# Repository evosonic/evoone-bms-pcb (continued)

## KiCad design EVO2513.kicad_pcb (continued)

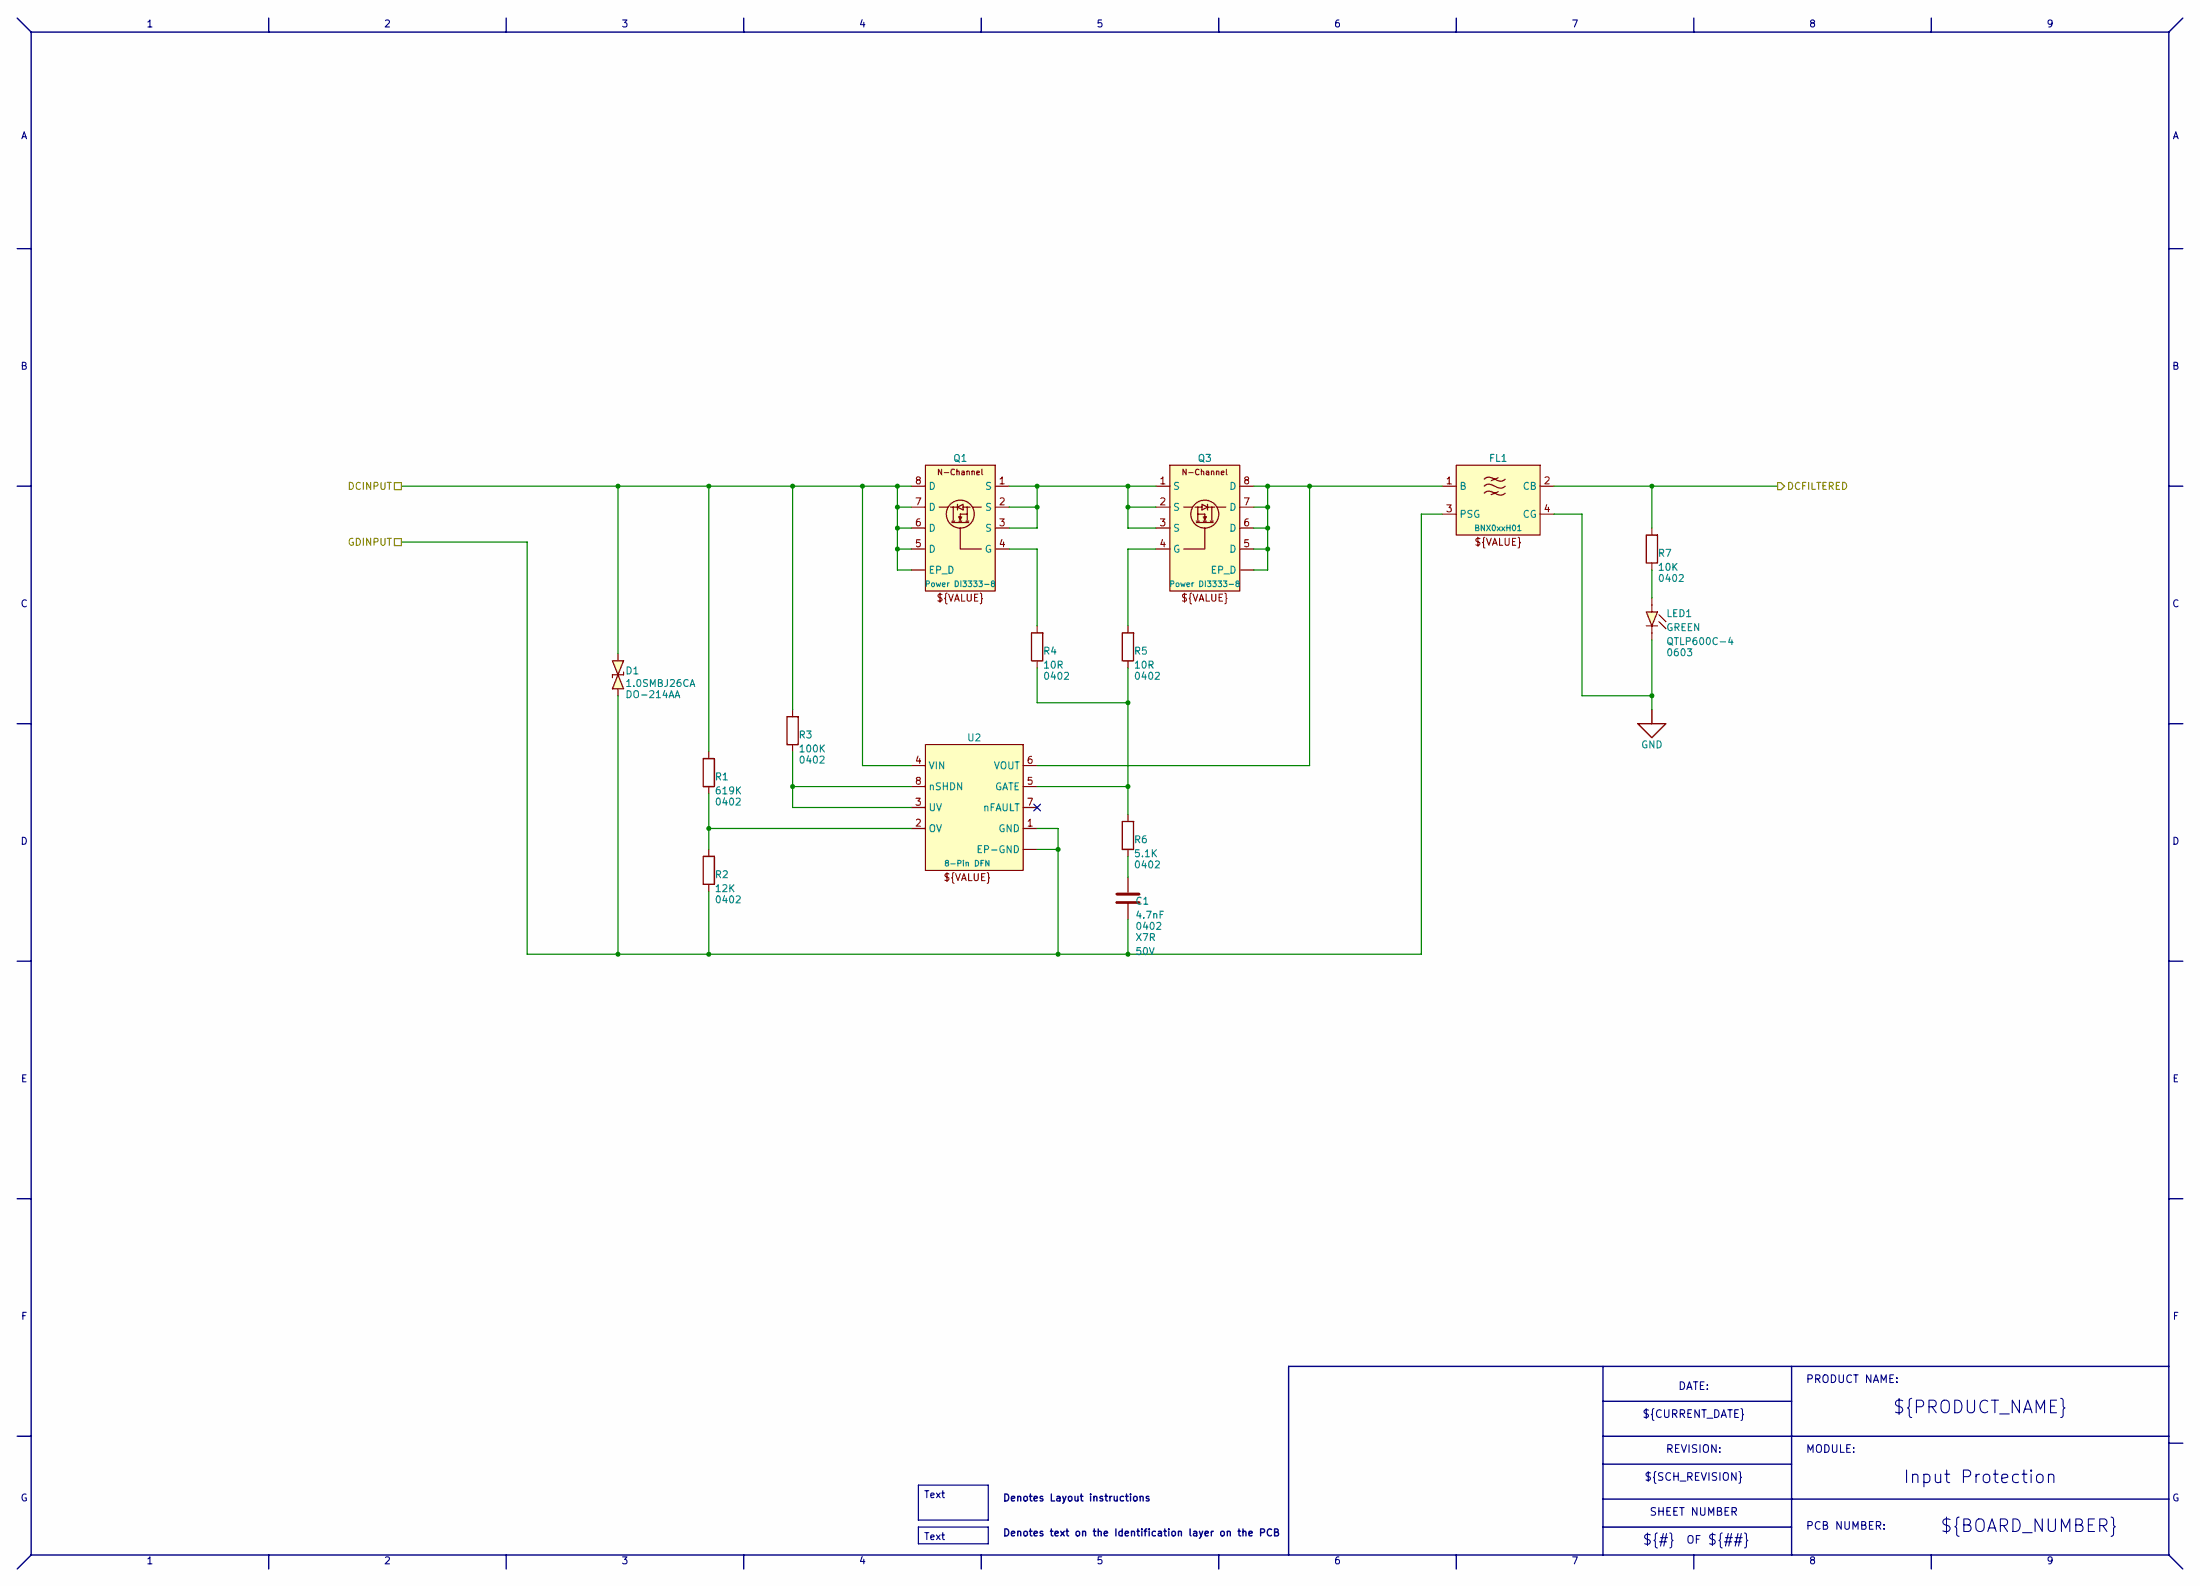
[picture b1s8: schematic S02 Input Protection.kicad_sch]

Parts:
C1: 4.7nF; C_0402_1005Metric; VOLTAGE 50V; MANUFACTURER_PN CC0402KRX7R9BB472
D1: 1.0SMBJ26CA; D_SMB; MANUFACTURER_PN 1.0SMBJ26CA
FL1: BNX024H01L; FILTER BNX0XXH01; MANUFACTURER_PN BNX024H01L
LED1: QTLP600C-4; LED_0603_1608Metric; MANUFACTURER_PN QTLP600C4TR
Q1, Q3: DMT6007LFG-7; Power DI3333-8 B3.3 x 3.3 P0.65 Tab 8-Pin; MANUFACTURER_PN DMT6007LFG-7
R1: 619K; R_0402_1005Metric; MANUFACTURER_PN RC0402FR-07619KL
R2: 12K; R_0402_1005Metric; MANUFACTURER_PN RC0402FR-0712KL
R3: 100K; R_0402_1005Metric; MANUFACTURER_PN RC0402FR-07100KL
R4, R5: 10R; R_0402_1005Metric; MANUFACTURER_PN RC0402FR-0710RL
R6: 5.1K; R_0402_1005Metric; MANUFACTURER_PN RC0402FR-075K1L
R7: 10K; R_0402_1005Metric; MANUFACTURER_PN RC0402FR-0710KL
U2: LTC4365; DFN B2.0 x 3.0 x 0.75 P0.5 8-Pin EP; MANUFACTURER_PN LTC4365IDDB#TRPBF

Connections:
/DCFILTERED: FL1.2 (CB), R7.2; also elsewhere on the board
/DCINPUT: D1.2 (A), Q1.5 (D), Q1.6 (D), Q1.7 (D), Q1.8 (D), Q1.9 (EP_D), R1.2, R3.2, U2.4 (VIN); also elsewhere on the board
/GDINPUT: C1.1, D1.1 (C), FL1.3 (PSG), R2.1, U2.1 (GND), U2.9 (EP-GND); also elsewhere on the board
GND: FL1.4 (CG), LED1.1 (C); also elsewhere on the board
unnamed: C1.2, R6.1
unnamed: FL1.1 (B), Q3.5 (D), Q3.6 (D), Q3.7 (D), Q3.8 (D), Q3.9 (EP_D), U2.6 (VOUT)
unnamed: LED1.2 (A), R7.1
unnamed: Q1.4 (G), R4.2
unnamed: Q1.1 (S), Q1.2 (S), Q1.3 (S), Q3.1 (S), Q3.2 (S), Q3.3 (S)
unnamed: Q3.4 (G), R5.2
unnamed: R4.1, R5.1, R6.2, U2.5 (GATE)
unnamed: R1.1, R2.2, U2.2 (OV)
unnamed: R3.1, U2.3 (UV), U2.8 (nSHDN)

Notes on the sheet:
Denotes Layout instructions
${PRODUCT_NAME}
${#}
Denotes text on the Identification layer on the PCB
REVISION:
${BOARD_NUMBER}
PRODUCT NAME:
DATE:
${CURRENT_DATE}
MODULE:
${##}
Input Protection
SHEET NUMBER
PCB NUMBER:
${SCH_REVISION}
Text

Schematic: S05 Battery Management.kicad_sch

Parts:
D4: BAT54A; SOT-23; MANUFACTURER_PN BAT54A_R1_00001
D9, D10: DT1240V3-04LP; Diodes_UDFN-10_1x2.5mm_P0.5mm; MANUFACTURER_PN DT1240V3-04LP-7; not fitted
Q8, Q9, Q10, Q11: DMT4011LFG; Power DI3333-8 B3.3 x 3.3 P0.65 Tab 8-Pin; MANUFACTURER_PN DMT4011LFG-7
Q12, Q13, Q14, Q15: DMP3007SCG-13; Diodes_PowerDI3333-8; MANUFACTURER_PN DMP3007SCG-13
R22: 1K; R_0402_1005Metric; MANUFACTURER_PN RC0402FR-071KL
R24, R25, R26, R27: 0R; R_0402_1005Metric; MANUFACTURER_PN RC0402JR-070RL
U1: LTC1960; QFN B5x7 P0-5 38-Pin EP; MANUFACTURER_PN LTC1960CUHF#PBF

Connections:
+5V: R22.2; also elsewhere on the board
/CLOCK1: R24.1; also elsewhere on the board
/CLOCK2: R26.1; also elsewhere on the board
/DATA1: R25.1; also elsewhere on the board
/DATA2: R27.1; also elsewhere on the board
/DCCHARGER: Q8.5 (D), Q8.6 (D), Q8.7 (D), Q8.8 (D), Q8.9 (EP_D), Q9.5 (D), Q9.6 (D), Q9.7 (D), Q9.8 (D), Q9.9 (EP_D); also elsewhere on the board
/DCPATH: Q14.5 (EP_D), Q15.5 (EP_D); also elsewhere on the board
/DSDA1: D9.2 (I/O2), D9.9 (I/O2), D9.[2,9] (I/O2), R25.2; also elsewhere on the board
/DSDA2: D10.1 (I/O1), D10.10 (I/O1), D10.[1,10] (I/O1), R27.2; also elsewhere on the board
/POS1: D4.1 (2C), Q10.5 (D), Q10.6 (D), Q10.7 (D), Q10.8 (D), Q10.9 (EP_D), Q12.5 (D), U1.29 (BAT1); also elsewhere on the board
/POS2: D4.2 (1C), Q11.5 (D), Q11.6 (D), Q11.7 (D), Q11.8 (D), Q11.9 (EP_D), Q13.5 (D), U1.28 (BAT2); also elsewhere on the board
/SAFE1: D9.5 (I/O4), D9.6 (I/O4); also elsewhere on the board
/SAFE2: D10.4 (I/O3), D10.7 (I/O3); also elsewhere on the board
/SCL1: D9.4 (I/O3), D9.7 (I/O3), D9.[4,7] (I/O3), R24.2; also elsewhere on the board
/SCL2: D10.2 (I/O2), D10.9 (I/O2), D10.[2,9] (I/O2), R26.2; also elsewhere on the board
GND: D9.1 (I/O1), D9.3 (VSS), D9.8 (VSS), D9.10 (I/O1), D10.3 (VSS), D10.5 (I/O4), D10.6 (I/O4), D10.8 (VSS); also elsewhere on the board
unnamed: D4.3 (A), R22.1
unnamed: Q8.4 (G), Q10.4 (G), U1.23 (GCH1)
unnamed: Q9.4 (G), Q11.4 (G), U1.24 (GCH2)
unnamed: Q12.4 (G), U1.35 (GB11)
unnamed: Q12.1 (S), Q12.2 (S), Q12.3 (S), Q14.1 (S), Q14.2 (S), Q14.3 (S)
unnamed: Q13.4 (G), U1.37 (GB21)
unnamed: Q13.1 (S), Q13.2 (S), Q13.3 (S), Q15.1 (S), Q15.2 (S), Q15.3 (S)
unnamed: Q14.4 (G), U1.34 (GB10)
unnamed: Q15.4 (G), U1.36 (GB20)
unnamed: Q8.1 (S), Q8.2 (S), Q8.3 (S), Q10.1 (S), Q10.2 (S), Q10.3 (S), U1.22 (SCH1)
unnamed: Q9.1 (S), Q9.2 (S), Q9.3 (S), Q11.1 (S), Q11.2 (S), Q11.3 (S), U1.25 (SCH2)

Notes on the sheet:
MODULE:
SHEET NUMBER
REVISION:
PRODUCT NAME:
${BOARD_NUMBER}
${#}
Denotes Layout instructions
${CURRENT_DATE}
DATE:
${##}
Denotes text on the Identification layer on the PCB
PCB NUMBER:
Battery Management
${SCH_REVISION}
R22 = 1K is the D4 battery-presence pull-up: an empty battery slot sits at about 5 V. Expected. Keep R22 at 1K
${PRODUCT_NAME}
Text

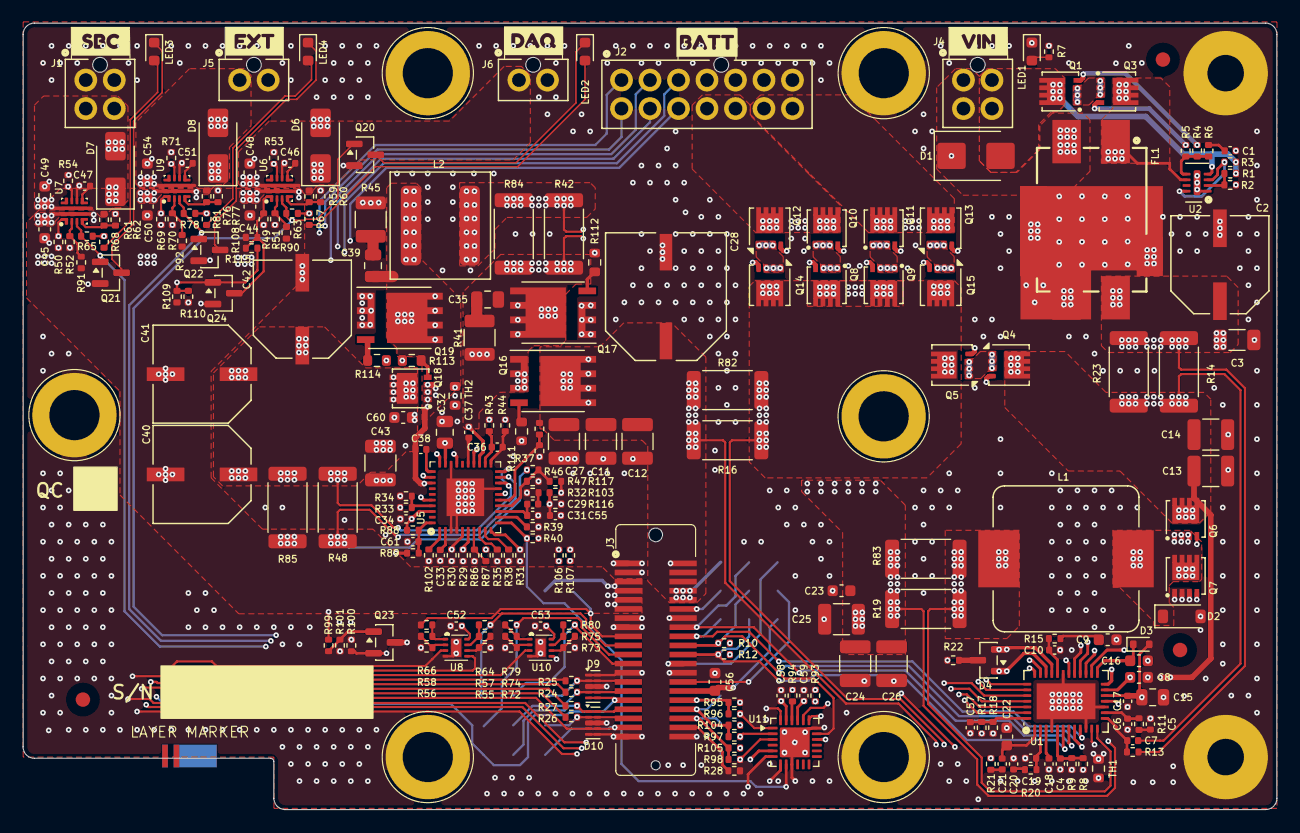
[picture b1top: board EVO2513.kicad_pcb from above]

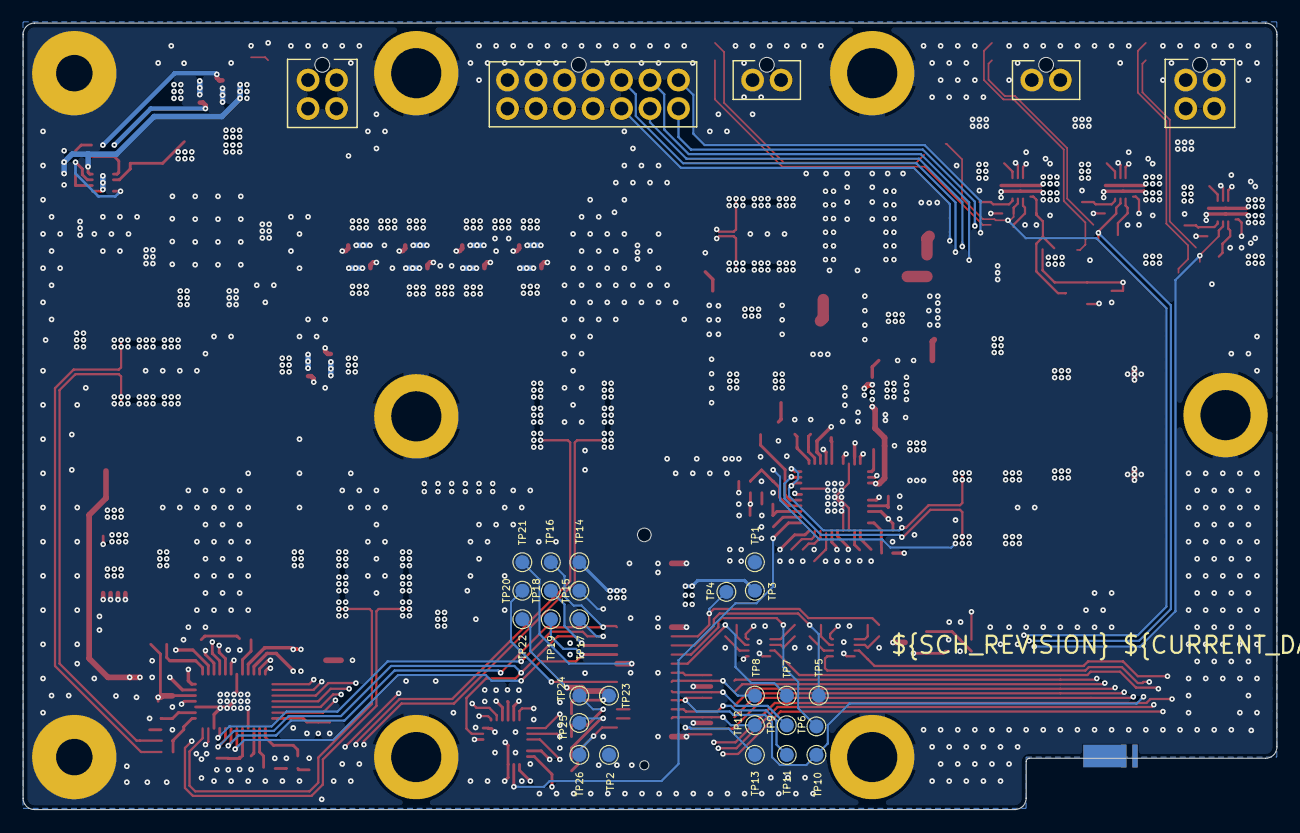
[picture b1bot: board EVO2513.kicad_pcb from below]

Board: 8 copper layers, 110.0 x 69.0 mm, 276 parts (26 on the bottom side), 154 nets.

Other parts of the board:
kibuzzard-6AD01E8C: G***; kibuzzard-6AD01E8C
kibuzzard-6AD01E71: G***; kibuzzard-6AD01E71
kibuzzard-6AD01EB3: G***; kibuzzard-6AD01EB3
kibuzzard-6AD01ECD: G***; kibuzzard-6AD01ECD
kibuzzard-6AD01EEF: G***; kibuzzard-6AD01EEF
